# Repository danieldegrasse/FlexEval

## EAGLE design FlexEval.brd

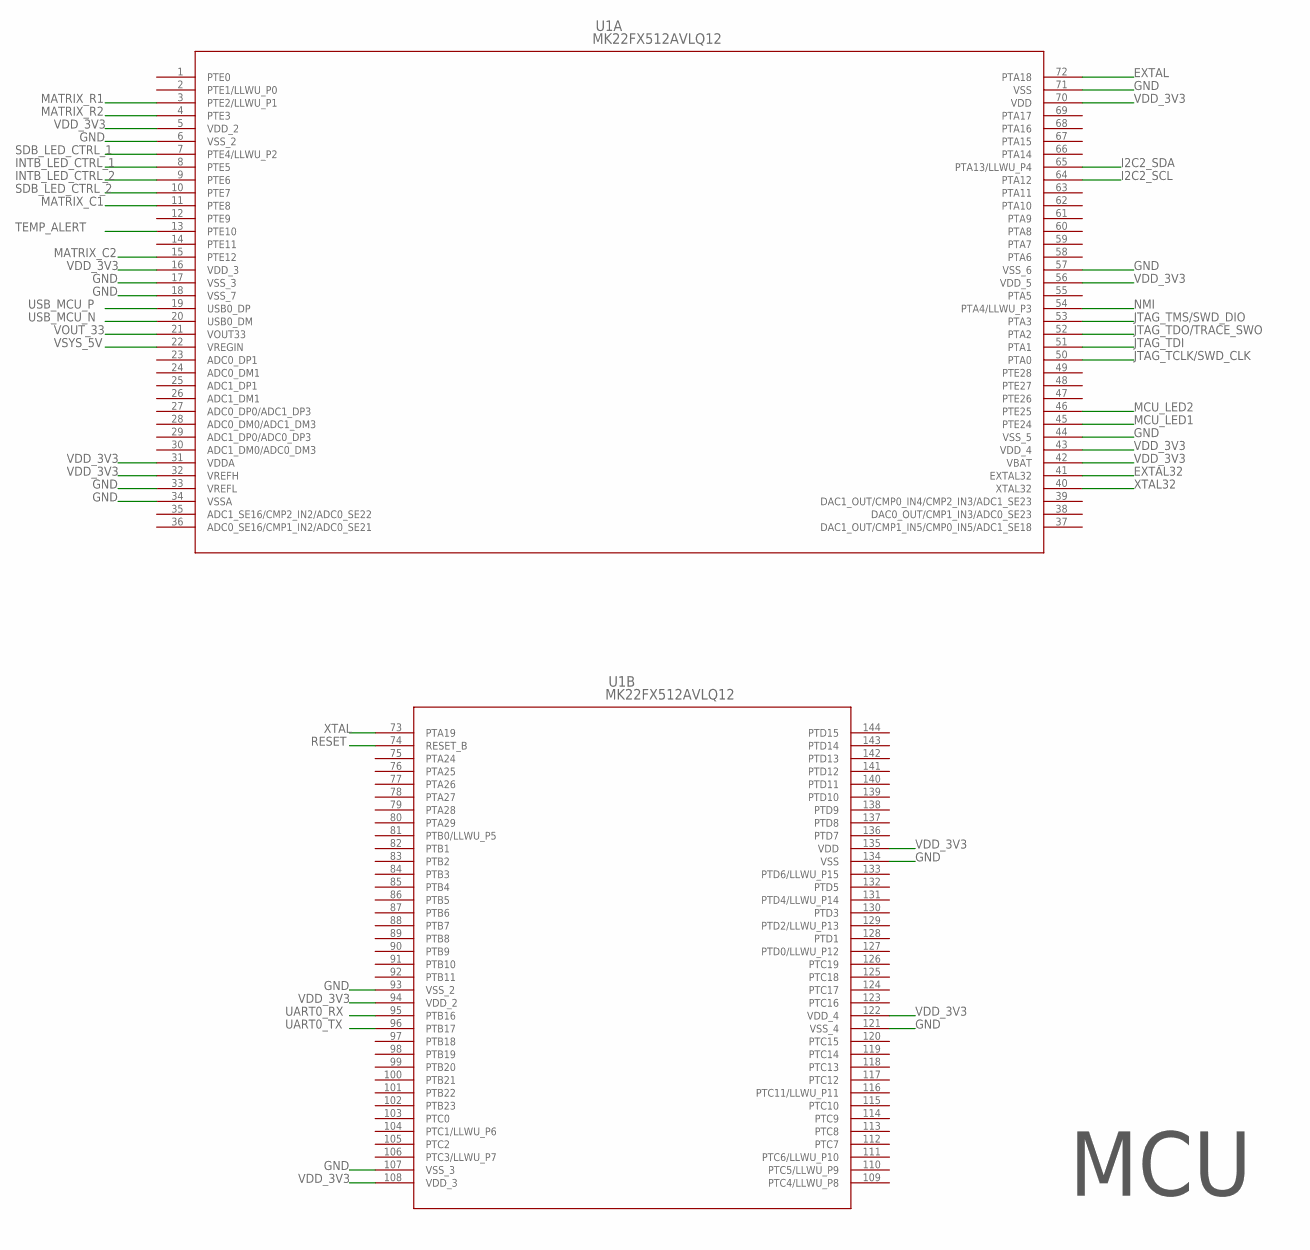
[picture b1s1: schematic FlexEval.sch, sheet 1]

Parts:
U1: MK22FX512AVLQ12; LQFP-144_20X20X1.6

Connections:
EXTAL: U1.72 (PTA18); also elsewhere on the board
EXTAL32: U1.41 (EXTAL32); also elsewhere on the board
GND: U1.6 (VSS_2), U1.17 (VSS_3), U1.18 (VSS_7), U1.33 (VREFL), U1.34 (VSSA), U1.44 (VSS_5), U1.57 (VSS_6), U1.71 (VSS), U1.93 (VSS_2), U1.107 (VSS_3), U1.121 (VSS_4), U1.134 (VSS); also elsewhere on the board
I2C2_SCL: U1.64 (PTA12); also elsewhere on the board
I2C2_SDA: U1.65 (PTA13/LLWU_P4); also elsewhere on the board
INTB_LED_CTRL_1: U1.8 (PTE5); also elsewhere on the board
INTB_LED_CTRL_2: U1.9 (PTE6); also elsewhere on the board
JTAG_TCLK/SWD_CLK: U1.50 (PTA0); also elsewhere on the board
JTAG_TDI: U1.51 (PTA1); also elsewhere on the board
JTAG_TDO/TRACE_SWO: U1.52 (PTA2); also elsewhere on the board
JTAG_TMS/SWD_DIO: U1.53 (PTA3); also elsewhere on the board
MATRIX_C1: U1.11 (PTE8); also elsewhere on the board
MATRIX_C2: U1.15 (PTE12); also elsewhere on the board
MATRIX_R1: U1.3 (PTE2/LLWU_P1); also elsewhere on the board
MATRIX_R2: U1.4 (PTE3); also elsewhere on the board
MCU_LED1: U1.45 (PTE24); also elsewhere on the board
MCU_LED2: U1.46 (PTE25); also elsewhere on the board
NMI: U1.54 (PTA4/LLWU_P3); also elsewhere on the board
RESET: U1.74 (RESET_B); also elsewhere on the board
SDB_LED_CTRL_1: U1.7 (PTE4/LLWU_P2); also elsewhere on the board
SDB_LED_CTRL_2: U1.10 (PTE7); also elsewhere on the board
TEMP_ALERT: U1.13 (PTE10); also elsewhere on the board
UART0_RX: U1.95 (PTB16); also elsewhere on the board
UART0_TX: U1.96 (PTB17); also elsewhere on the board
USB_MCU_N: U1.20 (USB0_DM); also elsewhere on the board
USB_MCU_P: U1.19 (USB0_DP); also elsewhere on the board
VDD_3V3: U1.5 (VDD_2), U1.16 (VDD_3), U1.31 (VDDA), U1.32 (VREFH), U1.42 (VBAT), U1.43 (VDD_4), U1.56 (VDD_5), U1.70 (VDD), U1.94 (VDD_2), U1.108 (VDD_3), U1.122 (VDD_4), U1.135 (VDD); also elsewhere on the board
VOUT_33: U1.21 (VOUT33); also elsewhere on the board
VSYS_5V: U1.22 (VREGIN); also elsewhere on the board
XTAL: U1.73 (PTA19); also elsewhere on the board
XTAL32: U1.40 (XTAL32); also elsewhere on the board

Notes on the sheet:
MCU

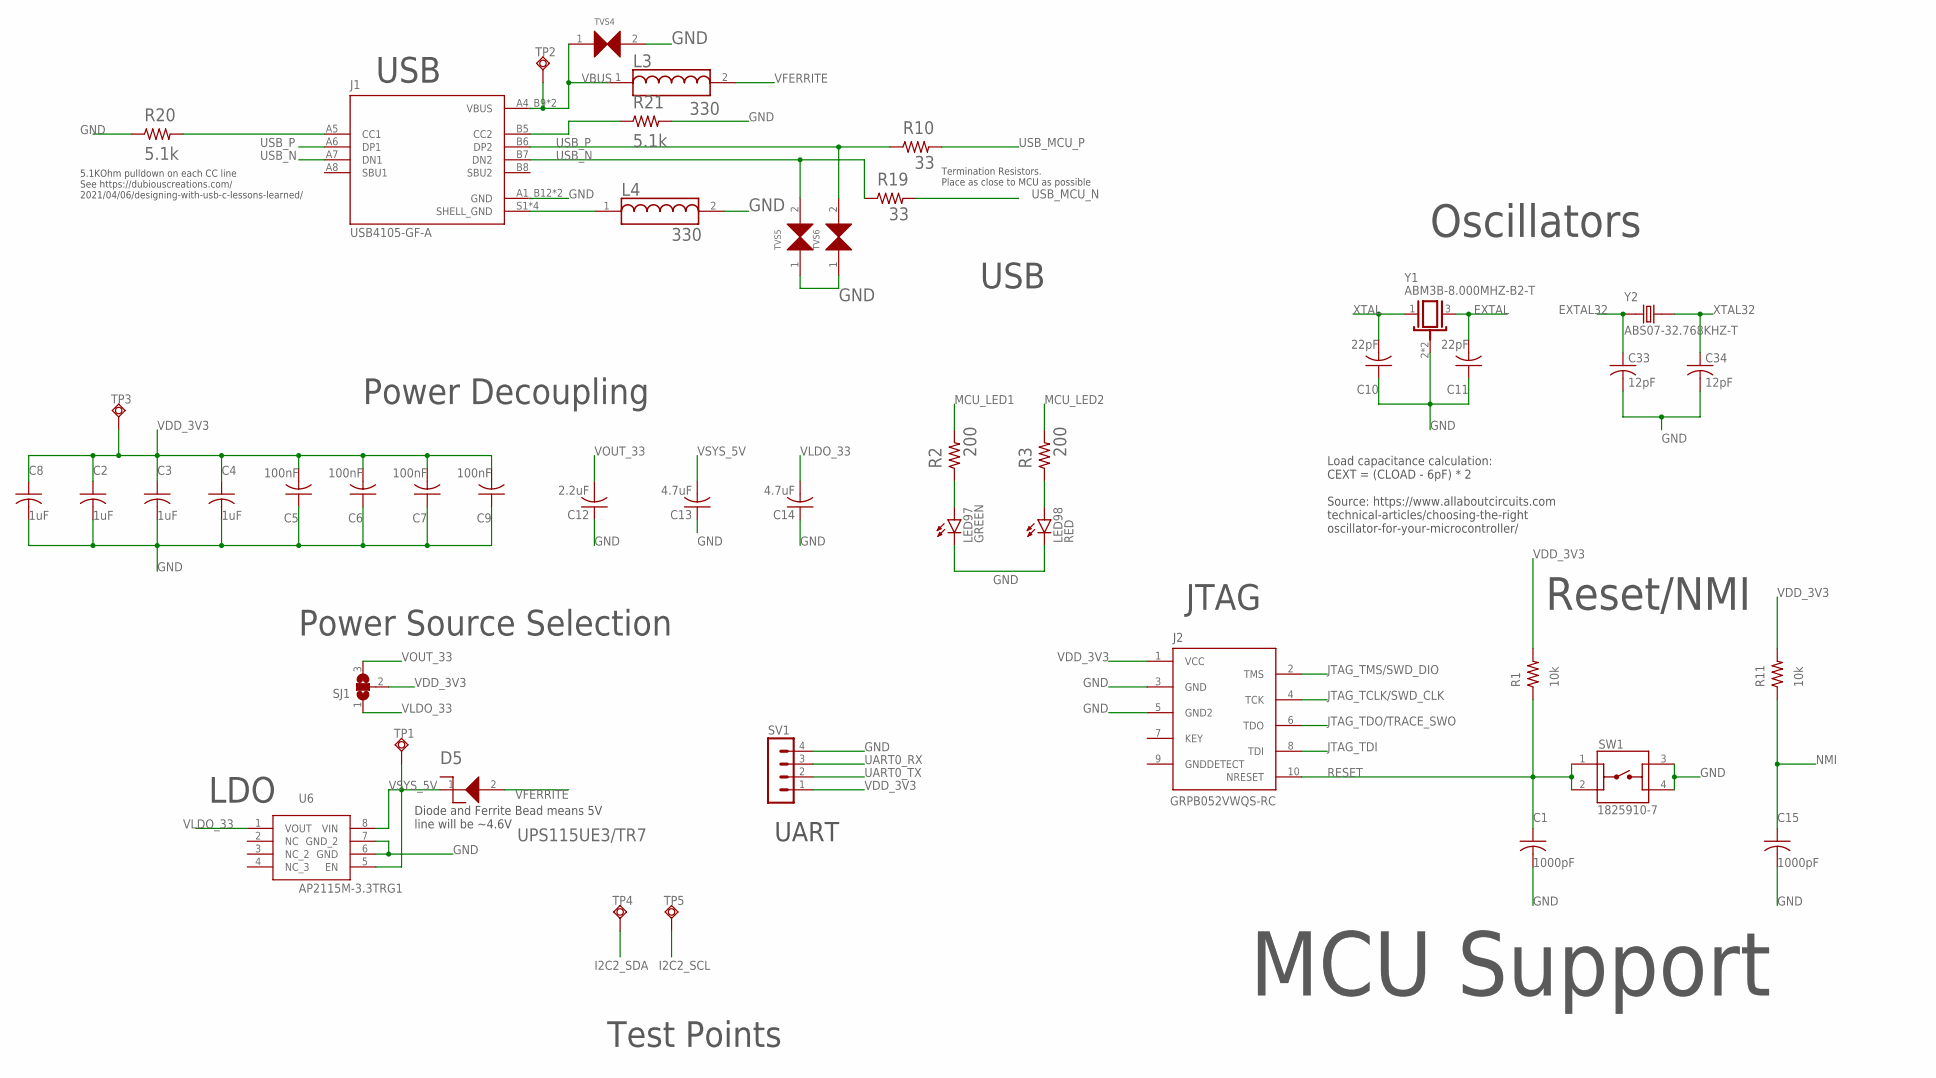
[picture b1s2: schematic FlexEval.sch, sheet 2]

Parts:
C1, C15: 1000pF; C1206
C2, C3, C4, C8: 1uF; C1206
C5, C6, C7, C9: 100nF; C1206
C10, C11: 22pF; C1206
C12: 2.2uF; C0805
C13, C14: 4.7uF; C0805
C33, C34: 12pF; C0805
D5: UPS115UE3/TR7
J1: USB4105-GF-A; GCT_USB4105-GF-A
J2: GRPB052VWQS-RC; DEBUG
L3, L4: 330; 78285333
LED97: GREEN; SML1206
LED98: RED; SML1206
R1, R11: 10k; R1206
R2, R3: 200; R0805
R10, R19: 33; R0805
R20, R21: 5.1k; R0805
SJ1: SJ2W; SJ_2
SV1: MA04-1
SW1: 1825910-7; SW_1825910-7
TP1, TP2, TP3, TP4, TP5: TPSQTP20R; TP20R
TVS4, TVS5, TVS6: 0603ESDA2-TR2
U6: AP2115M-3.3TRG1; SOIC127P600X175-8N
Y1: ABM3B-8.000MHZ-B2-T; OSC_ABM3B-8.000MHZ-B2-T
Y2: ABS07-32.768KHZ-T; XTAL_ABS07-32.768KHZ-T

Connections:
EXTAL: C11.2, Y1.3; also elsewhere on the board
EXTAL32: C33.1, Y2.1; also elsewhere on the board
GND: C1.2, C2.2, C3.2, C4.2, C5.1, C6.1, C7.1, C8.2, C9.1, C10.1, C11.1, C12.1, C13.1, C14.1, C15.2, C33.2, C34.2, J1.A1_B12 (GND), J1.B1_A12 (GND), J2.3 (GND), J2.5 (GND2), L4.2, LED97.C, LED98.C, R20.1, R21.2, SV1.4, SW1.3, SW1.4, TVS4.2, TVS5.1, TVS6.1, U6.6 (GND), U6.7 (GND_2), Y1.2 (GND), Y1.4 (GND); also elsewhere on the board
I2C2_SCL: TP5.TP; also elsewhere on the board
I2C2_SDA: TP4.TP; also elsewhere on the board
JTAG_TCLK/SWD_CLK: J2.4 (TCK); also elsewhere on the board
JTAG_TDI: J2.8 (TDI); also elsewhere on the board
JTAG_TDO/TRACE_SWO: J2.6 (TDO); also elsewhere on the board
JTAG_TMS/SWD_DIO: J2.2 (TMS); also elsewhere on the board
MCU_LED1: R2.2; also elsewhere on the board
MCU_LED2: R3.2; also elsewhere on the board
unnamed: LED97.A, R2.1
unnamed: LED98.A, R3.1
unnamed: J1.S1 (SHELL_GND), J1.S2 (SHELL_GND), J1.S3 (SHELL_GND), J1.S4 (SHELL_GND), L4.1
unnamed: J1.B5 (CC2), R21.1
unnamed: J1.A5 (CC1), R20.2
NMI: C15.1, R11.1; also elsewhere on the board
RESET: C1.1, J2.10 (NRESET), R1.1, SW1.1, SW1.2; also elsewhere on the board
UART0_RX: SV1.3; also elsewhere on the board
UART0_TX: SV1.2; also elsewhere on the board
USB_MCU_N: R19.2; also elsewhere on the board
USB_MCU_P: R10.2; also elsewhere on the board
USB_N: J1.A7 (DN1), J1.B7 (DN2), R19.1, TVS5.2
USB_P: J1.A6 (DP1), J1.B6 (DP2), R10.1, TVS6.2
VBUS: J1.A4_B9 (VBUS), J1.B4_A9 (VBUS), L3.1, TP2.TP, TVS4.1
VDD_3V3: C2.1, C3.1, C4.1, C5.2, C6.2, C7.2, C8.1, C9.2, J2.1 (VCC), R1.2, R11.2, SJ1.2, SV1.1, TP3.TP; also elsewhere on the board
VFERRITE: D5.2, L3.2
VLDO_33: C14.2, SJ1.1, U6.1 (VOUT)
VOUT_33: C12.2, SJ1.3; also elsewhere on the board
VSYS_5V: C13.2, D5.1, TP1.TP, U6.5 (EN), U6.8 (VIN); also elsewhere on the board
XTAL: C10.2, Y1.1; also elsewhere on the board
XTAL32: C34.1, Y2.2; also elsewhere on the board

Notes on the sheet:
USB
JTAG
UART
Power Source Selection
Power Decoupling
LDO
Reset/NMI
Oscillators
MCU Support
Diode and Ferrite Bead means 5V line will be ~4.6V
Load capacitance calculation: CEXT = (CLOAD - 6pF) * 2 Source: https://www.allaboutcircuits.com technical-articles/choosing-the-right oscillator-for-your-microcontroller/
5.1KOhm pulldown on each CC line See https://dubiouscreations.com/ 2021/04/06/designing-with-usb-c-lessons-learned/
Termination Resistors. Place as close to MCU as possible
Test Points

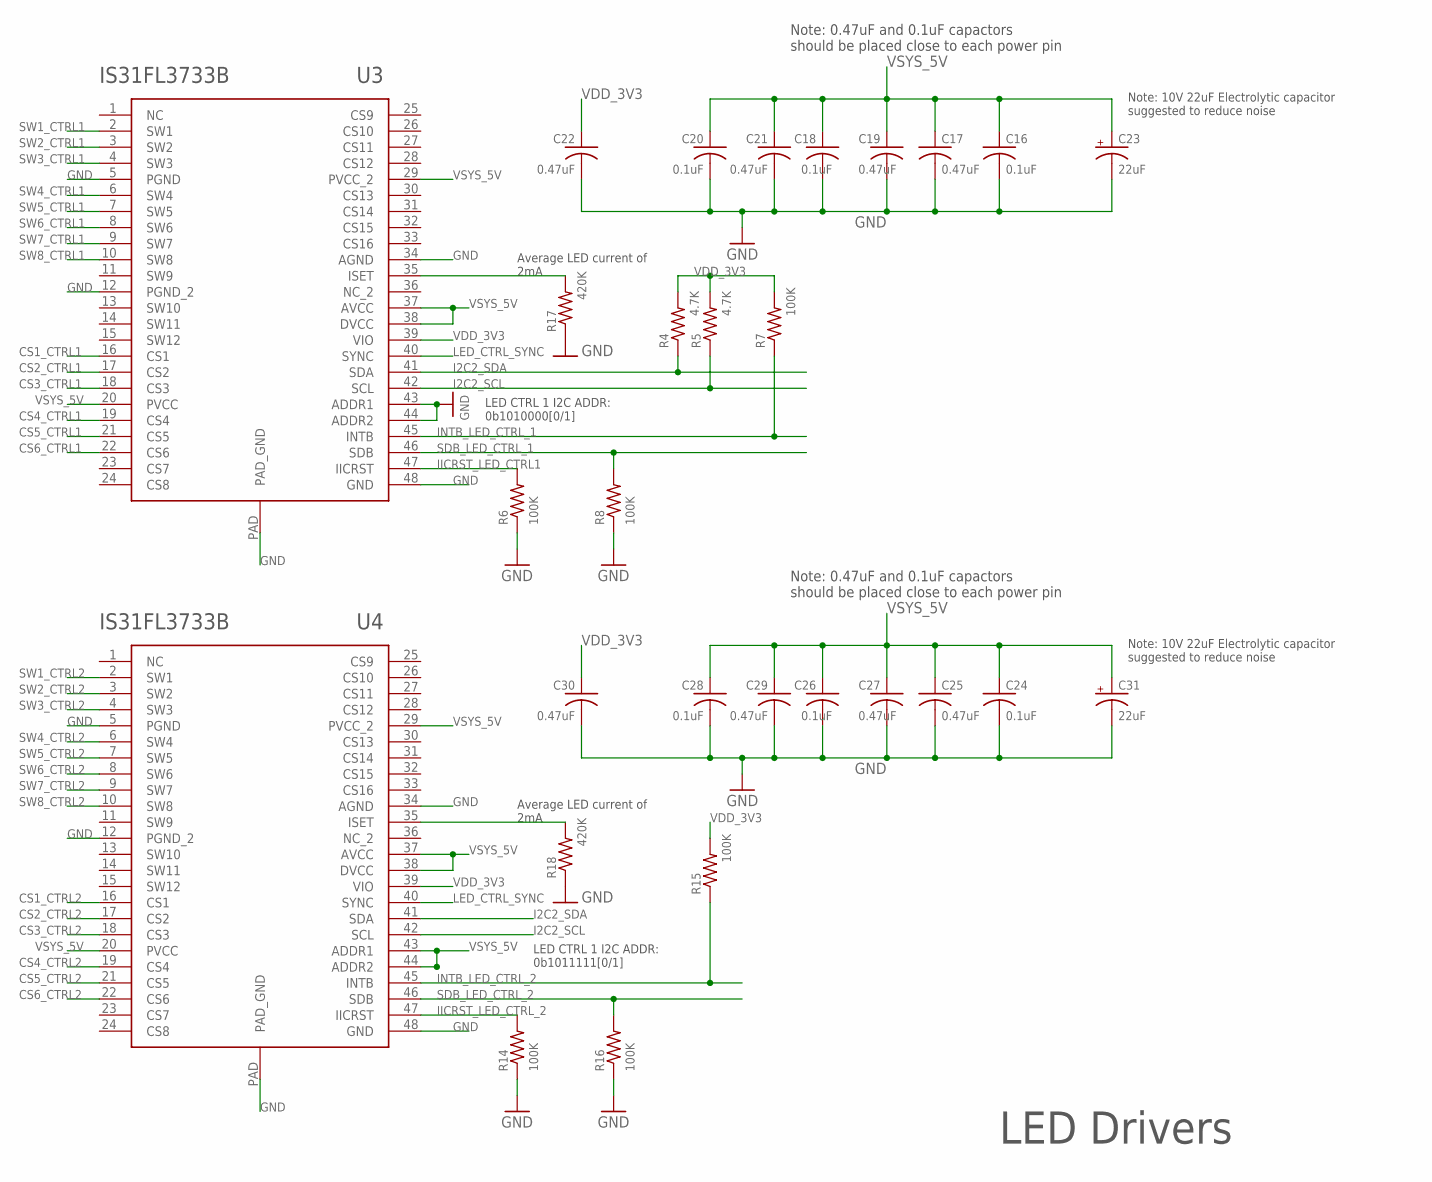
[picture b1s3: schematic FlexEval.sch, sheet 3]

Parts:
C16, C18, C20, C24, C26, C28: 0.1uF; C0805
C17, C19, C21, C22, C25, C27, C29, C30: 0.47uF; C0805
C23, C31: 22uF; 860020672011
R4, R5: 4.7K; R0805
R6, R7, R8, R14, R15, R16: 100K; R0805
R17, R18: 420K; R0805
U3, U4: IS31FL3733B-TQLS4

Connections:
CS1_CTRL1: U3.16 (CS1); also elsewhere on the board
CS1_CTRL2: U4.16 (CS1); also elsewhere on the board
CS2_CTRL1: U3.17 (CS2); also elsewhere on the board
CS2_CTRL2: U4.17 (CS2); also elsewhere on the board
CS3_CTRL1: U3.18 (CS3); also elsewhere on the board
CS3_CTRL2: U4.18 (CS3); also elsewhere on the board
CS4_CTRL1: U3.19 (CS4); also elsewhere on the board
CS4_CTRL2: U4.19 (CS4); also elsewhere on the board
CS5_CTRL1: U3.21 (CS5); also elsewhere on the board
CS5_CTRL2: U4.21 (CS5); also elsewhere on the board
CS6_CTRL1: U3.22 (CS6); also elsewhere on the board
CS6_CTRL2: U4.22 (CS6); also elsewhere on the board
GND: C16.2, C17.2, C18.2, C19.2, C20.2, C21.2, C22.2, C23.-, C24.2, C25.2, C26.2, C27.2, C28.2, C29.2, C30.2, C31.-, R6.1, R8.1, R14.1, R16.1, R17.1, R18.1, U3.5 (PGND), U3.12 (PGND_2), U3.34 (AGND), U3.43 (ADDR1), U3.44 (ADDR2), U3.48 (GND), U3.PAD (PAD_GND), U4.5 (PGND), U4.12 (PGND_2), U4.34 (AGND), U4.48 (GND), U4.PAD (PAD_GND); also elsewhere on the board
I2C2_SCL: R5.1, U3.42 (SCL), U4.42 (SCL); also elsewhere on the board
I2C2_SDA: R4.1, U3.41 (SDA), U4.41 (SDA); also elsewhere on the board
IICRST_LED_CTRL1: R6.2, U3.47 (IICRST)
IICRST_LED_CTRL_2: R14.2, U4.47 (IICRST)
INTB_LED_CTRL_1: R7.1, U3.45 (INTB); also elsewhere on the board
INTB_LED_CTRL_2: R15.1, U4.45 (INTB); also elsewhere on the board
LED_CTRL_SYNC: U3.40 (SYNC), U4.40 (SYNC)
unnamed: R17.2, U3.35 (ISET)
unnamed: R18.2, U4.35 (ISET)
SDB_LED_CTRL_1: R8.2, U3.46 (SDB); also elsewhere on the board
SDB_LED_CTRL_2: R16.2, U4.46 (SDB); also elsewhere on the board
SW1_CTRL1: U3.2 (SW1); also elsewhere on the board
SW1_CTRL2: U4.2 (SW1); also elsewhere on the board
SW2_CTRL1: U3.3 (SW2); also elsewhere on the board
SW2_CTRL2: U4.3 (SW2); also elsewhere on the board
SW3_CTRL1: U3.4 (SW3); also elsewhere on the board
SW3_CTRL2: U4.4 (SW3); also elsewhere on the board
SW4_CTRL1: U3.6 (SW4); also elsewhere on the board
SW4_CTRL2: U4.6 (SW4); also elsewhere on the board
SW5_CTRL1: U3.7 (SW5); also elsewhere on the board
SW5_CTRL2: U4.7 (SW5); also elsewhere on the board
SW6_CTRL1: U3.8 (SW6); also elsewhere on the board
SW6_CTRL2: U4.8 (SW6); also elsewhere on the board
SW7_CTRL1: U3.9 (SW7); also elsewhere on the board
SW7_CTRL2: U4.9 (SW7); also elsewhere on the board
SW8_CTRL1: U3.10 (SW8); also elsewhere on the board
SW8_CTRL2: U4.10 (SW8); also elsewhere on the board
VDD_3V3: C22.1, C30.1, R4.2, R5.2, R7.2, R15.2, U3.39 (VIO), U4.39 (VIO); also elsewhere on the board
VSYS_5V: C16.1, C17.1, C18.1, C19.1, C20.1, C21.1, C23.+, C24.1, C25.1, C26.1, C27.1, C28.1, C29.1, C31.+, U3.20 (PVCC), U3.29 (PVCC_2), U3.37 (AVCC), U3.38 (DVCC), U4.20 (PVCC), U4.29 (PVCC_2), U4.37 (AVCC), U4.38 (DVCC), U4.43 (ADDR1), U4.44 (ADDR2); also elsewhere on the board

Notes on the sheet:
LED Drivers
Note: 10V 22uF Electrolytic capacitor suggested to reduce noise
LED CTRL 1 I2C ADDR: 0b1010000[0/1]
Note: 0.47uF and 0.1uF capactors should be placed close to each power pin
LED CTRL 1 I2C ADDR: 0b1011111[0/1]
Average LED current of 2mA

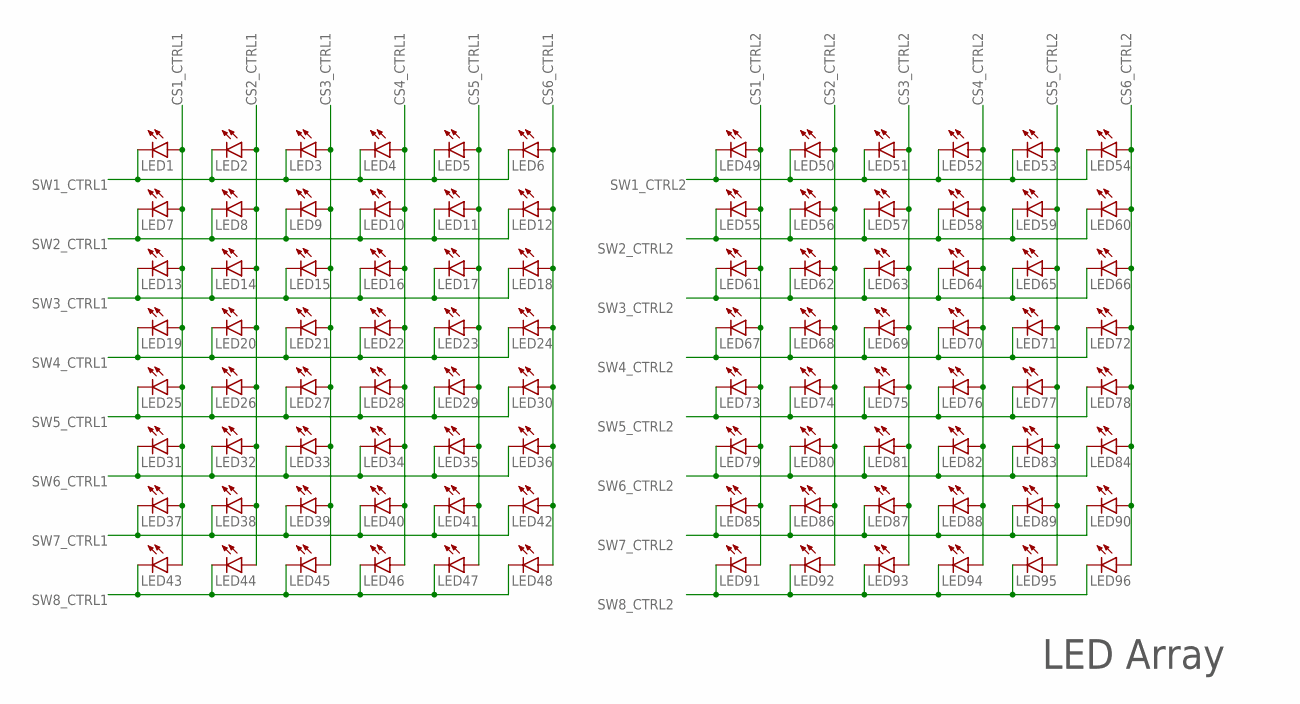
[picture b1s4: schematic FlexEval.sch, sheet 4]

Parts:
LED1, LED2, LED3, LED4, LED5, LED6, LED7, LED8, LED9, LED10, LED11, LED12, LED13, LED14, LED15, LED16, LED17, LED18, LED19, LED20, LED21, LED22, LED23, LED24, LED25, LED26, LED27, LED28, LED29, LED30, LED31, LED32, LED33, LED34, LED35, LED36, LED37, LED38, LED39, LED40, LED41, LED42, LED43, LED44, LED45, LED46, LED47, LED48, LED49, LED50, LED51, LED52, LED53, LED54, LED55, LED56, LED57, LED58, LED59, LED60, LED61, LED62, LED63, LED64, LED65, LED66, LED67, LED68, LED69, LED70, LED71, LED72, LED73, LED74, LED75, LED76, LED77, LED78, LED79, LED80, LED81, LED82, LED83, LED84, LED85, LED86, LED87, LED88, LED89, LED90, LED91, LED92, LED93, LED94, LED95, LED96: LED3MM

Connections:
CS1_CTRL1: LED1.A, LED7.A, LED13.A, LED19.A, LED25.A, LED31.A, LED37.A, LED43.A; also elsewhere on the board
CS1_CTRL2: LED49.A, LED55.A, LED61.A, LED67.A, LED73.A, LED79.A, LED85.A, LED91.A; also elsewhere on the board
CS2_CTRL1: LED2.A, LED8.A, LED14.A, LED20.A, LED26.A, LED32.A, LED38.A, LED44.A; also elsewhere on the board
CS2_CTRL2: LED50.A, LED56.A, LED62.A, LED68.A, LED74.A, LED80.A, LED86.A, LED92.A; also elsewhere on the board
CS3_CTRL1: LED3.A, LED9.A, LED15.A, LED21.A, LED27.A, LED33.A, LED39.A, LED45.A; also elsewhere on the board
CS3_CTRL2: LED51.A, LED57.A, LED63.A, LED69.A, LED75.A, LED81.A, LED87.A, LED93.A; also elsewhere on the board
CS4_CTRL1: LED4.A, LED10.A, LED16.A, LED22.A, LED28.A, LED34.A, LED40.A, LED46.A; also elsewhere on the board
CS4_CTRL2: LED52.A, LED58.A, LED64.A, LED70.A, LED76.A, LED82.A, LED88.A, LED94.A; also elsewhere on the board
CS5_CTRL1: LED5.A, LED11.A, LED17.A, LED23.A, LED29.A, LED35.A, LED41.A, LED47.A; also elsewhere on the board
CS5_CTRL2: LED53.A, LED59.A, LED65.A, LED71.A, LED77.A, LED83.A, LED89.A, LED95.A; also elsewhere on the board
CS6_CTRL1: LED6.A, LED12.A, LED18.A, LED24.A, LED30.A, LED36.A, LED42.A, LED48.A; also elsewhere on the board
CS6_CTRL2: LED54.A, LED60.A, LED66.A, LED72.A, LED78.A, LED84.A, LED90.A, LED96.A; also elsewhere on the board
SW1_CTRL1: LED1.K (C), LED2.K (C), LED3.K (C), LED4.K (C), LED5.K (C), LED6.K (C); also elsewhere on the board
SW1_CTRL2: LED49.K (C), LED50.K (C), LED51.K (C), LED52.K (C), LED53.K (C), LED54.K (C); also elsewhere on the board
SW2_CTRL1: LED7.K (C), LED8.K (C), LED9.K (C), LED10.K (C), LED11.K (C), LED12.K (C); also elsewhere on the board
SW2_CTRL2: LED55.K (C), LED56.K (C), LED57.K (C), LED58.K (C), LED59.K (C), LED60.K (C); also elsewhere on the board
SW3_CTRL1: LED13.K (C), LED14.K (C), LED15.K (C), LED16.K (C), LED17.K (C), LED18.K (C); also elsewhere on the board
SW3_CTRL2: LED61.K (C), LED62.K (C), LED63.K (C), LED64.K (C), LED65.K (C), LED66.K (C); also elsewhere on the board
SW4_CTRL1: LED19.K (C), LED20.K (C), LED21.K (C), LED22.K (C), LED23.K (C), LED24.K (C); also elsewhere on the board
SW4_CTRL2: LED67.K (C), LED68.K (C), LED69.K (C), LED70.K (C), LED71.K (C), LED72.K (C); also elsewhere on the board
SW5_CTRL1: LED25.K (C), LED26.K (C), LED27.K (C), LED28.K (C), LED29.K (C), LED30.K (C); also elsewhere on the board
SW5_CTRL2: LED73.K (C), LED74.K (C), LED75.K (C), LED76.K (C), LED77.K (C), LED78.K (C); also elsewhere on the board
SW6_CTRL1: LED31.K (C), LED32.K (C), LED33.K (C), LED34.K (C), LED35.K (C), LED36.K (C); also elsewhere on the board
SW6_CTRL2: LED79.K (C), LED80.K (C), LED81.K (C), LED82.K (C), LED83.K (C), LED84.K (C); also elsewhere on the board
SW7_CTRL1: LED37.K (C), LED38.K (C), LED39.K (C), LED40.K (C), LED41.K (C), LED42.K (C); also elsewhere on the board
SW7_CTRL2: LED85.K (C), LED86.K (C), LED87.K (C), LED88.K (C), LED89.K (C), LED90.K (C); also elsewhere on the board
SW8_CTRL1: LED43.K (C), LED44.K (C), LED45.K (C), LED46.K (C), LED47.K (C), LED48.K (C); also elsewhere on the board
SW8_CTRL2: LED91.K (C), LED92.K (C), LED93.K (C), LED94.K (C), LED95.K (C), LED96.K (C); also elsewhere on the board

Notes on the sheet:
LED Array

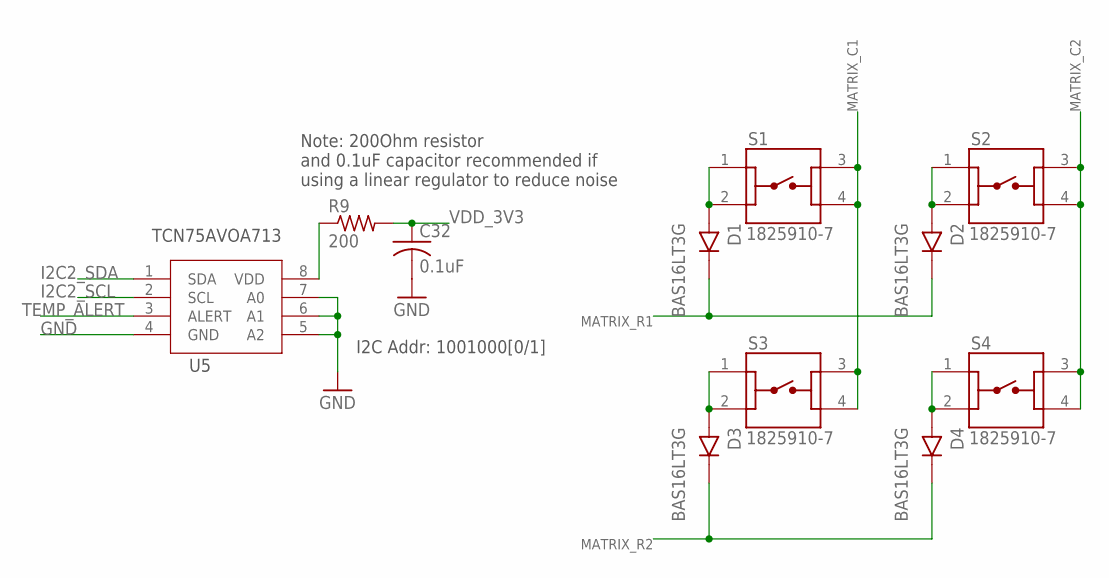
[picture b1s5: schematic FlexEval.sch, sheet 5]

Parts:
C32: 0.1uF; C0805
D1, D2, D3, D4: BAS16LT3G; SOT95P240X111-3N
R9: 200; R0805
S1, S2, S3, S4: 1825910-7; SW_1825910-7
U5: SOIC127P600X175-8N

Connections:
GND: C32.2, U5.4 (GND), U5.5 (A2), U5.6 (A1), U5.7 (A0); also elsewhere on the board
I2C2_SCL: U5.2 (SCL); also elsewhere on the board
I2C2_SDA: U5.1 (SDA); also elsewhere on the board
MATRIX_C1: S1.3, S1.4, S3.3, S3.4; also elsewhere on the board
MATRIX_C2: S2.3, S2.4, S4.3, S4.4; also elsewhere on the board
MATRIX_R1: D1.3 (C), D2.3 (C); also elsewhere on the board
MATRIX_R2: D3.3 (C), D4.3 (C); also elsewhere on the board
unnamed: D1.1 (A), S1.1, S1.2
unnamed: D2.1 (A), S2.1, S2.2
unnamed: D3.1 (A), S3.1, S3.2
unnamed: D4.1 (A), S4.1, S4.2
unnamed: R9.1, U5.8 (VDD)
TEMP_ALERT: U5.3 (ALERT); also elsewhere on the board
VDD_3V3: C32.1, R9.2; also elsewhere on the board

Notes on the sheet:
I2C Addr: 1001000[0/1]
Note: 200Ohm resistor and 0.1uF capacitor recommended if using a linear regulator to reduce noise

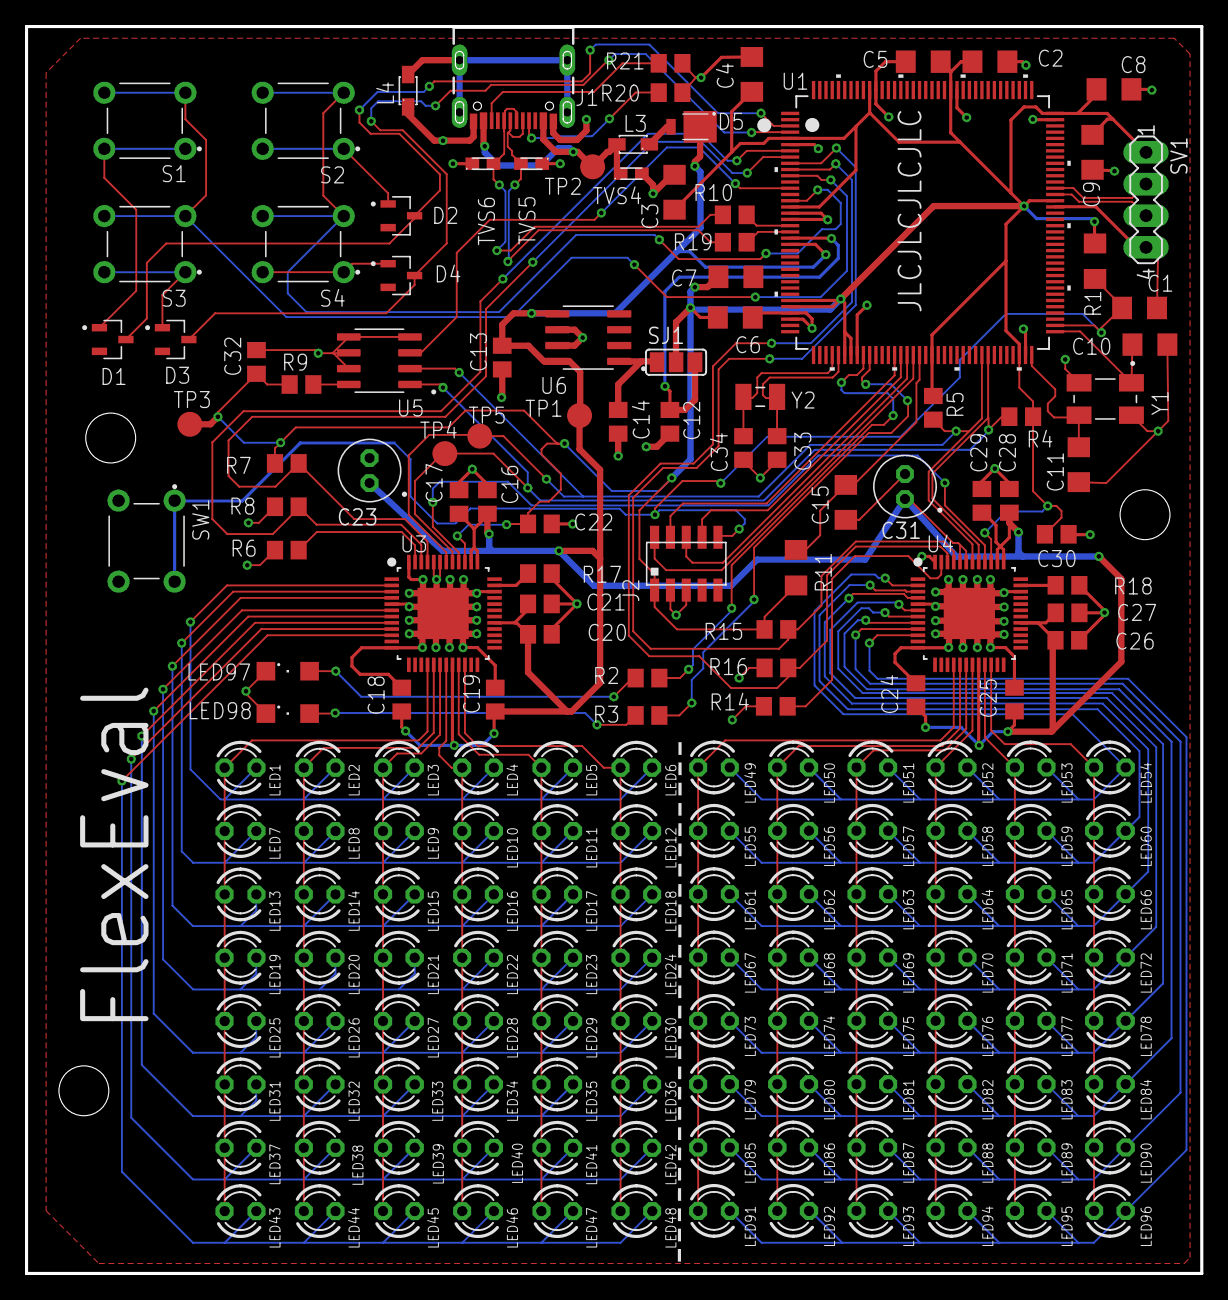
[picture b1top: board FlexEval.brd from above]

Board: 2 copper layers, 94.2 x 100.0 mm, 182 parts (0 on the bottom side), 79 nets.

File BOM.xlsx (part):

Part | Value | Device | Package | Description | A1_MIN | AVAILABILITY | A_MAX | A_MIN | A_NOM | B_MAX | B_MIN | B_NOM | COMMENT | CONFIGURATION_POLE-THROW | CONTACT_CURRENT_RATING | CPU | D1_MAX | D1_MIN | D1_NOM | D2_MAX | DESCRIPTION | DMAX | DMIN | DNOM | D_MAX | D_MIN | D_NOM | E1_MAX | E1_MIN | E1_NOM | E2_MAX | EMAX | EMIN | ENOM | EU_ROHS_COMPLIANCE | E_MAX | E_MIN | E_NOM | FLASHKB | L1_MAX | L1_MIN | L1_NOM | L_MAX | L_MIN | L_NOM | MANUFACTURER | MANUFACTURER_PART_NUMBER | MAXFREQUENCY | MF | MP | MPN | OC_FARNELL | OC_NEWARK | PACKAGE | PACKAGE_TYPE | PINCOUNT | PINS | PIN_COUNT | POPULARITY | PRICE | PURCHASE-URL | SNAPEDA_PACKAGE_ID | SRAMKB | STANDARD | VACANCIES | VENDOR
C1 | 1000pF | C-USC1206 | C1206 | CAPACITOR, American symbol
C10 | 22pF | C-USC1206 | C1206 | CAPACITOR, American symbol
C11 | 22pF | C-USC1206 | C1206 | CAPACITOR, American symbol
C12 | 2.2uF | C-USC0805 | C0805 | CAPACITOR, American symbol
C13 | 4.7uF | C-USC0805 | C0805 | CAPACITOR, American symbol
C14 | 4.7uF | C-USC0805 | C0805 | CAPACITOR, American symbol
C15 | 1000pF | C-USC1206 | C1206 | CAPACITOR, American symbol
C16 | 0.1uF | C-USC0805 | C0805 | CAPACITOR, American symbol
C17 | 0.47uF | C-USC0805 | C0805 | CAPACITOR, American symbol
C18 | 0.1uF | C-USC0805 | C0805 | CAPACITOR, American symbol
C19 | 0.47uF | C-USC0805 | C0805 | CAPACITOR, American symbol
C2 | 1uF | C-USC1206 | C1206 | CAPACITOR, American symbol
C20 | 0.1uF | C-USC0805 | C0805 | CAPACITOR, American symbol
C21 | 0.47uF | C-USC0805 | C0805 | CAPACITOR, American symbol
C22 | 0.47uF | C-USC0805 | C0805 | CAPACITOR, American symbol
C23 | 22uF | 860020672011 | 860020672011 | 22uF 50V Electrolytic Capacitor Wurth 860020672011
C24 | 0.1uF | C-USC0805 | C0805 | CAPACITOR, American symbol
C25 | 0.47uF | C-USC0805 | C0805 | CAPACITOR, American symbol
C26 | 0.1uF | C-USC0805 | C0805 | CAPACITOR, American symbol
C27 | 0.47uF | C-USC0805 | C0805 | CAPACITOR, American symbol
C28 | 0.1uF | C-USC0805 | C0805 | CAPACITOR, American symbol
C29 | 0.47uF | C-USC0805 | C0805 | CAPACITOR, American symbol
C3 | 1uF | C-USC1206 | C1206 | CAPACITOR, American symbol
C30 | 0.47uF | C-USC0805 | C0805 | CAPACITOR, American symbol
C31 | 22uF | 860020672011 | 860020672011 | 22uF 50V Electrolytic Capacitor Wurth 860020672011
C32 | 0.1uF | C-USC0805 | C0805 | CAPACITOR, American symbol
C33 | 12pF | C-USC0805 | C0805 | CAPACITOR, American symbol
C34 | 12pF | C-USC0805 | C0805 | CAPACITOR, American symbol
C4 | 1uF | C-USC1206 | C1206 | CAPACITOR, American symbol
C5 | 100nF | C-USC1206 | C1206 | CAPACITOR, American symbol
C6 | 100nF | C-USC1206 | C1206 | CAPACITOR, American symbol
C7 | 100nF | C-USC1206 | C1206 | CAPACITOR, American symbol
C8 | 1uF | C-USC1206 | C1206 | CAPACITOR, American symbol
C9 | 100nF | C-USC1206 | C1206 | CAPACITOR, American symbol
D1 | BAS16LT3G | BAS16LT3G | SOT95P240X111-3N | Diode Small Signal Switching 100V 0.2A Automotive 3-Pin SOT-23 T/R Check prices |  | In Stock |  |  |  |  |  |  |  |  |  |  |  |  |  |  | Diode Standard 100V 200mA (DC) Surface Mount SOT-23-3 (TO-236) |  |  |  |  |  |  |  |  |  |  |  |  |  |  |  |  |  |  |  |  |  |  |  |  |  |  |  | ON Semiconductor | BAS16LT3G |  |  |  | SOT-23-3 ON Semiconductor |  |  |  |  |  | None
D2 | BAS16LT3G | BAS16LT3G | SOT95P240X111-3N | Diode Small Signal Switching 100V 0.2A Automotive 3-Pin SOT-23 T/R Check prices |  | In Stock |  |  |  |  |  |  |  |  |  |  |  |  |  |  | Diode Standard 100V 200mA (DC) Surface Mount SOT-23-3 (TO-236) |  |  |  |  |  |  |  |  |  |  |  |  |  |  |  |  |  |  |  |  |  |  |  |  |  |  |  | ON Semiconductor | BAS16LT3G |  |  |  | SOT-23-3 ON Semiconductor |  |  |  |  |  | None
D3 | BAS16LT3G | BAS16LT3G | SOT95P240X111-3N | Diode Small Signal Switching 100V 0.2A Automotive 3-Pin SOT-23 T/R Check prices |  | In Stock |  |  |  |  |  |  |  |  |  |  |  |  |  |  | Diode Standard 100V 200mA (DC) Surface Mount SOT-23-3 (TO-236) |  |  |  |  |  |  |  |  |  |  |  |  |  |  |  |  |  |  |  |  |  |  |  |  |  |  |  | ON Semiconductor | BAS16LT3G |  |  |  | SOT-23-3 ON Semiconductor |  |  |  |  |  | None
D4 | BAS16LT3G | BAS16LT3G | SOT95P240X111-3N | Diode Small Signal Switching 100V 0.2A Automotive 3-Pin SOT-23 T/R Check prices |  | In Stock |  |  |  |  |  |  |  |  |  |  |  |  |  |  | Diode Standard 100V 200mA (DC) Surface Mount SOT-23-3 (TO-236) |  |  |  |  |  |  |  |  |  |  |  |  |  |  |  |  |  |  |  |  |  |  |  |  |  |  |  | ON Semiconductor | BAS16LT3G |  |  |  | SOT-23-3 ON Semiconductor |  |  |  |  |  | None
D5 | UPS115UE3/TR7 | UPS115UE3/TR7 | UPS115UE3/TR7 | Schottky diode (15V, 220mV@1A)
J1 | USB4105-GF-A | USB4105-GF-A | GCT_USB4105-GF-A | USB-C (USB TYPE-C) USB 2.0 Receptacle Connector 24 (16+8 Dummy) Position Surfac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 |  | In Stock |  |  |  |  |  |  |  |  |  |  |  |  |  |  | USB-C (USB TYPE-C) USB 2.0 Receptacle Connector 24 (16+8 Dummy) Position Surfac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 | Through Hole |  |  |  |  |  |  |  |  |  |  |  |  |  |  |  |  |  |  |  |  |  |  |  |  |  |  |  | GCT | USB4105-GF-A |  |  |  | None |  |  |  |  |  | None | https://pricing.snapeda.com/search/part/USB4105-GF-A/?ref=eda
J2 | GRPB052VWQS-RC | GRPB052VWQS-RC | DEBUG | CONN HEADER SMD 10POS 1.27MM (SWD debug header) | 10PS | DL | SMD | AU" |  | In Stock |  |  |  |  |  |  |  |  |  |  |  |  |  |  | Connector Header Surface Mount 10 position 0.050 (1.27mm) |  |  |  |  |  |  |  |  |  |  |  |  |  |  |  |  |  |  |  |  |  |  |  |  |  |  |  | Sullins Connector | GRPB052VWQS-RC |  |  |  | None |  |  |  |  |  | None | https://pricing.snapeda.com/search/part/GRPB052VWQS-RC/?ref=eda
L3 | 330 | 782853331SMD | 78285333 | 330mOhm Ferrite Bead
L4 | 330 | 782853331SMD | 78285333 | 330mOhm Ferrite Bead
LED1 |  | LED3MM | LED3MM | 3mm Flangeless LED |  |  |  |  |  |  |  |  |  |  |  |  |  |  |  |  |  |  |  |  |  |  |  |  |  |  |  |  |  |  |  |  |  |  |  |  |  |  |  |  |  |  |  |  |  |  |  |  |  |  |  |  |  |  | 97
LED10 |  | LED3MM | LED3MM | 3mm Flangeless LED |  |  |  |  |  |  |  |  |  |  |  |  |  |  |  |  |  |  |  |  |  |  |  |  |  |  |  |  |  |  |  |  |  |  |  |  |  |  |  |  |  |  |  |  |  |  |  |  |  |  |  |  |  |  | 97
LED11 |  | LED3MM | LED3MM | 3mm Flangeless LED |  |  |  |  |  |  |  |  |  |  |  |  |  |  |  |  |  |  |  |  |  |  |  |  |  |  |  |  |  |  |  |  |  |  |  |  |  |  |  |  |  |  |  |  |  |  |  |  |  |  |  |  |  |  | 97
LED12 |  | LED3MM | LED3MM | 3mm Flangeless LED |  |  |  |  |  |  |  |  |  |  |  |  |  |  |  |  |  |  |  |  |  |  |  |  |  |  |  |  |  |  |  |  |  |  |  |  |  |  |  |  |  |  |  |  |  |  |  |  |  |  |  |  |  |  | 97
LED13 |  | LED3MM | LED3MM | 3mm Flangeless LED |  |  |  |  |  |  |  |  |  |  |  |  |  |  |  |  |  |  |  |  |  |  |  |  |  |  |  |  |  |  |  |  |  |  |  |  |  |  |  |  |  |  |  |  |  |  |  |  |  |  |  |  |  |  | 97
LED14 |  | LED3MM | LED3MM | 3mm Flangeless LED |  |  |  |  |  |  |  |  |  |  |  |  |  |  |  |  |  |  |  |  |  |  |  |  |  |  |  |  |  |  |  |  |  |  |  |  |  |  |  |  |  |  |  |  |  |  |  |  |  |  |  |  |  |  | 97
LED15 |  | LED3MM | LED3MM | 3mm Flangeless LED |  |  |  |  |  |  |  |  |  |  |  |  |  |  |  |  |  |  |  |  |  |  |  |  |  |  |  |  |  |  |  |  |  |  |  |  |  |  |  |  |  |  |  |  |  |  |  |  |  |  |  |  |  |  | 97
LED16 |  | LED3MM | LED3MM | 3mm Flangeless LED |  |  |  |  |  |  |  |  |  |  |  |  |  |  |  |  |  |  |  |  |  |  |  |  |  |  |  |  |  |  |  |  |  |  |  |  |  |  |  |  |  |  |  |  |  |  |  |  |  |  |  |  |  |  | 97
LED17 |  | LED3MM | LED3MM | 3mm Flangeless LED |  |  |  |  |  |  |  |  |  |  |  |  |  |  |  |  |  |  |  |  |  |  |  |  |  |  |  |  |  |  |  |  |  |  |  |  |  |  |  |  |  |  |  |  |  |  |  |  |  |  |  |  |  |  | 97
LED18 |  | LED3MM | LED3MM | 3mm Flangeless LED |  |  |  |  |  |  |  |  |  |  |  |  |  |  |  |  |  |  |  |  |  |  |  |  |  |  |  |  |  |  |  |  |  |  |  |  |  |  |  |  |  |  |  |  |  |  |  |  |  |  |  |  |  |  | 97
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
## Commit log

2022-10-15 Initial commit: added all required library files and board design
    Board design passes JLCPCB DRC, and Eagle default ERC. Board is
    fully routed, but final manufacturing checks are not complete, and
    no BOM is generated.
2022-10-16 schematic: update resistors and capacitors to Eagle libraries
    Updated all resistors and capacitors to use Eagle libraries instead
    of custom SnapEDA variants for each component. This should improve
    flexibility of the design, since SMD packages for passives are standard
    sizes.
2022-10-16 board: replaced Electrolytic Capactitors
    Replaced electrolytic capacitors with real models, instead of
    Eagle's default library
2022-10-16 BOM: added initial BOM. This should hopefully remain final.
    Board is passing DRC, and all components that need to be ordered
    are currently in stock.
2022-10-16 board: added test points and debug LEDs
    Added two debug LEDs, and test points on I2C and voltage signals. BOM
    updated with 2 additional 200 Ohm resistors and 2 1206 LEDs
2022-10-16 libraries : updated USB4105-GF-A connector footprint, removed USB4105 lib
    Removed USB4105 lib, as that library is not in use.
    Updated USB4105-GF-A footprint with the following patches:
    - extended all pads to 1.35mm (beyond manufacturer recommendation of 1.15)
    to make hand soldering easier
    - moved GND connectors up by 0.1mm to fix clearance issue with drilled
    holes
2022-10-16 board: cleaned up text locations and switched to vector fonts
    Cleaned up board text locations (and added some decoration).
    Switched all fonts on tNames layer to vector fonts.
    Added "JLCJLCJLCJLC" to silkscreen, for JLCPCB order number
    location
2022-10-16 Manufacturing: generated gerber files
    Generated gerber files for JLCPCB. Board should be ready for order.
2022-10-16 BOM: added extra quantities to items for order
    Added extra quantities to order list, in case a part is lost
    or damaged during assembly.
2023-06-17 board: created layout and schematic PDFS
    Created layout and schematic PDFs, to make search board components
    easier.
